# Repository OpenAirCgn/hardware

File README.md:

# hardware
eagle schematics for mics sensor

current openairnode-hw > https://github.com/everykey/openairnode-hw

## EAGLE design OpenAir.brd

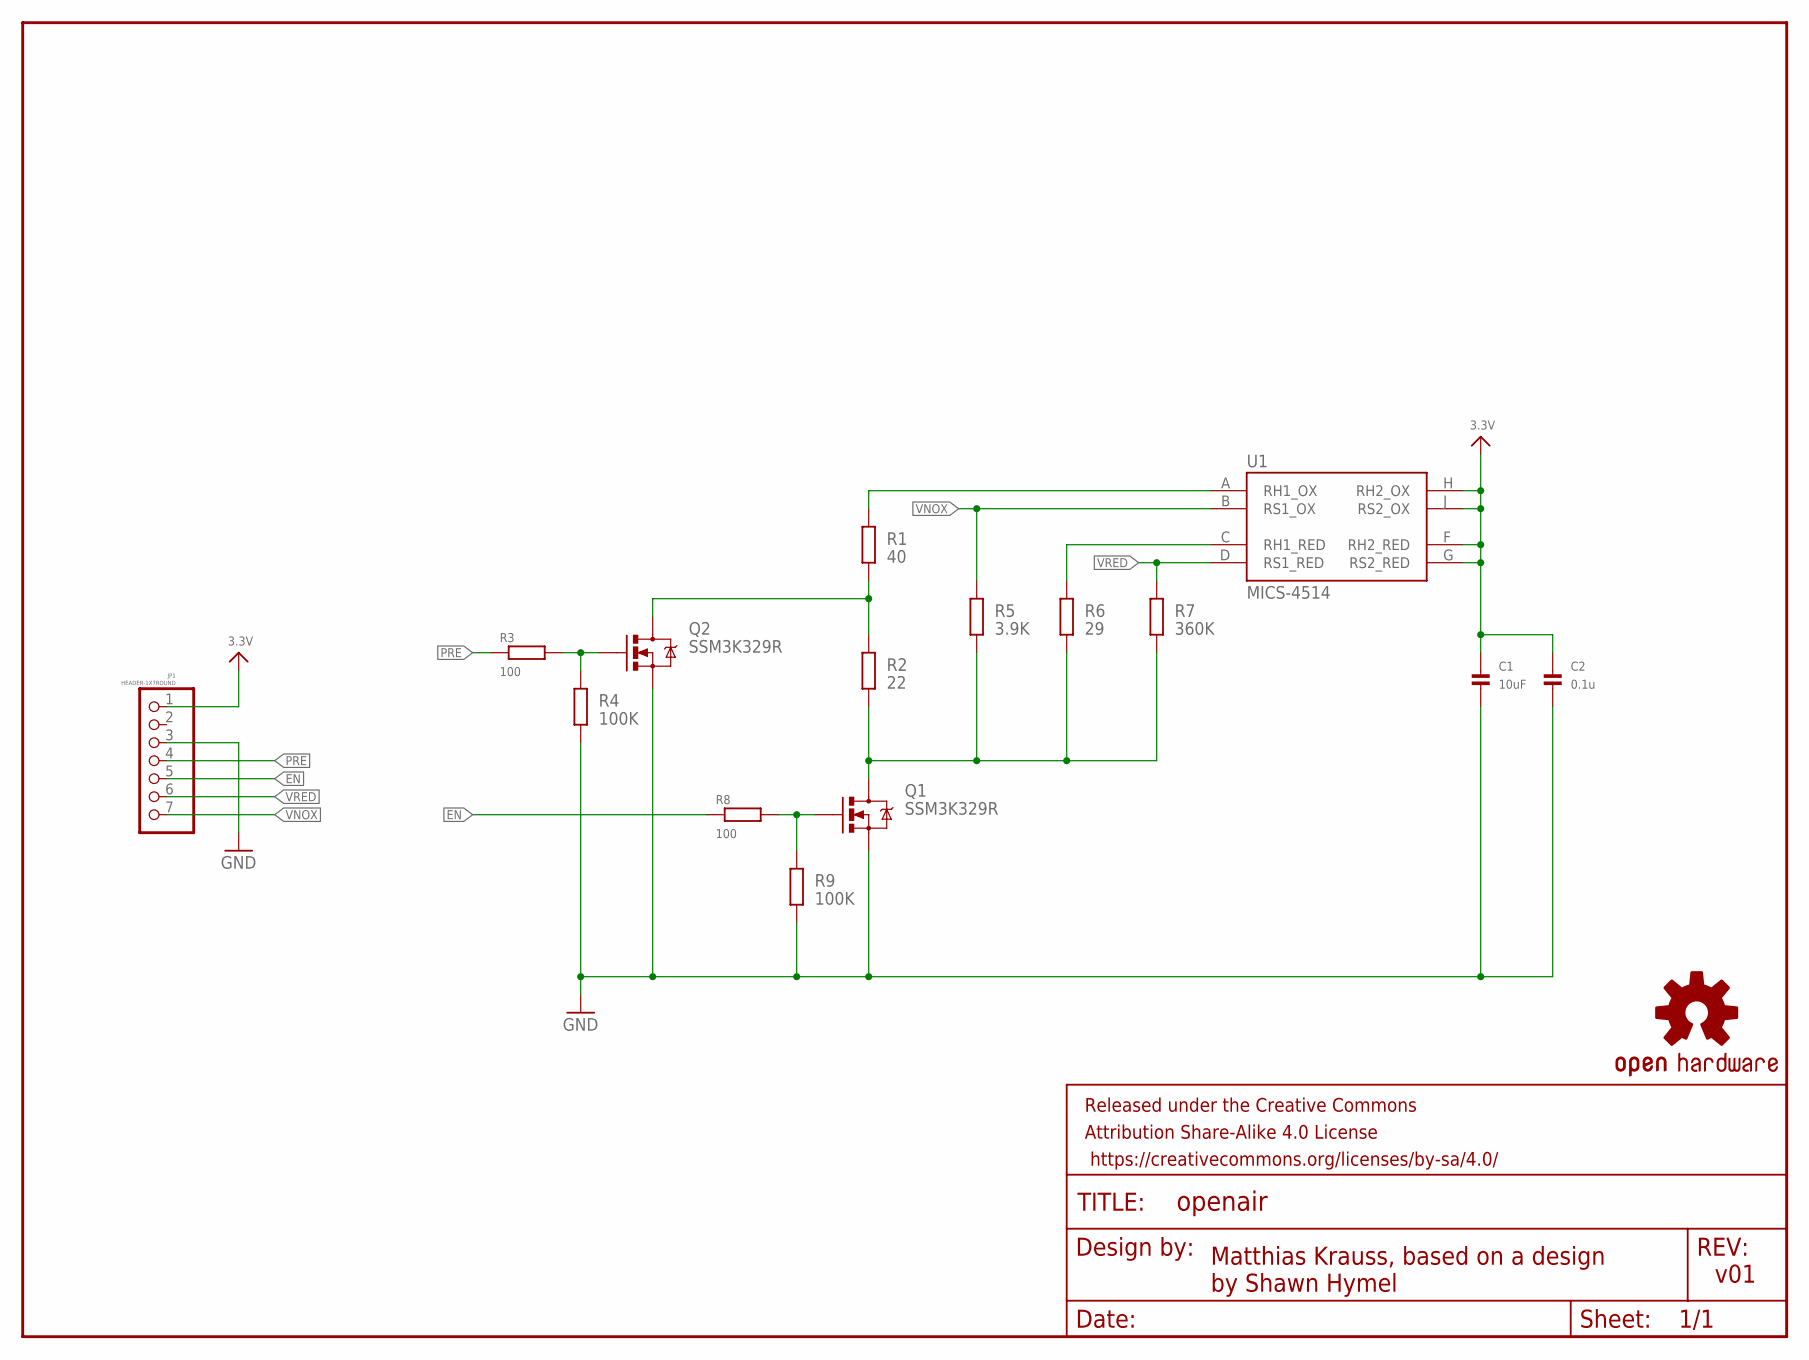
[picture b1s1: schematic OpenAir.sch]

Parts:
C1: 10uF; 0603
C2: 0.1u; 0603
FRAME1: FRAME-LETTER; CREATIVE_COMMONS
JP1: HEADER-1X7ROUND; 1X07_ROUND
LOGO1: OSHW-LOGOS; OSHW-LOGO-S
Q1, Q2: SSM3K329R; SOT23-3
R1: 40; 0603
R2: 22; 0603
R3, R8: 100; 0603
R4, R9: 100K; 0603
R5: 3.9K; 0603
R6: 29; 0603
R7: 360K; 0603
U1: MICS-4514; MICS_10-SMD

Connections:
3.3V: C1.1, C2.1, JP1.1, U1.F (RH2_RED), U1.G (RS2_RED), U1.H (RH2_OX), U1.J (RS2_OX)
EN: JP1.5, R8.1
EN_GATE: Q1.1 (G), R8.2, R9.2
GND: C1.2, C2.2, JP1.3, Q1.2 (S), Q2.2 (S), R4.1, R9.1
GND_EN: Q1.3 (D), R2.1, R5.1, R6.1, R7.1
unnamed: R1.2, U1.A (RH1_OX)
unnamed: R6.2, U1.C (RH1_RED)
PRE: JP1.4, R3.1
PREHEAT_GATE: Q2.1 (G), R3.2, R4.2
PREHEAT_POWER: Q2.3 (D), R1.1, R2.2
VNOX: JP1.7, R5.2, U1.B (RS1_OX)
VRED: JP1.6, R7.2, U1.D (RS1_RED)

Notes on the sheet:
v01
Matthias Krauss, based on a design by Shawn Hymel

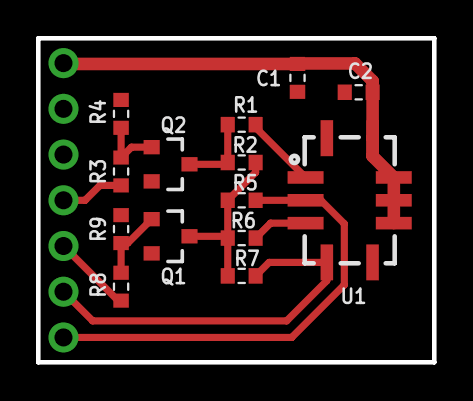
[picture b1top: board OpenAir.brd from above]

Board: 2 copper layers, 22.0 x 18.0 mm, 17 parts (1 on the bottom side), 12 nets.

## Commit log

2017-11-30 add new hardware submodule

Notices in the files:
parts and their libraries:
SparkFun-Aesthetics: Licensing: Creative Commons ShareAlike 4.0 International - https://creativecommons.org/licenses/by-sa/4.0
SparkFun-Aesthetics: Released under the Creative Commons Attribution Share-Alike 4.0 License
SparkFun-Aesthetics: https://creativecommons.org/licenses/by-sa/4.0
